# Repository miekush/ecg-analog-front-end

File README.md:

# ECG_Analog_Front_End
Simple Analog Front End for Electrocardiography using INA126 and OPA2337

# License

MKE supports the open source hardware community by sharing hardware design files freely on GitHub!

Please support MKE by purchasing products on [Tindie](https://www.tindie.com/stores/mkengineering/)!

Designed by Mike Kushnerik for MKEngineering

Licensed under [Creative Commons Attribution-ShareAlike CC BY-SA 3.0](http://creativecommons.org/licenses/by-sa/3.0/)

All text above must be included in any redistribution!

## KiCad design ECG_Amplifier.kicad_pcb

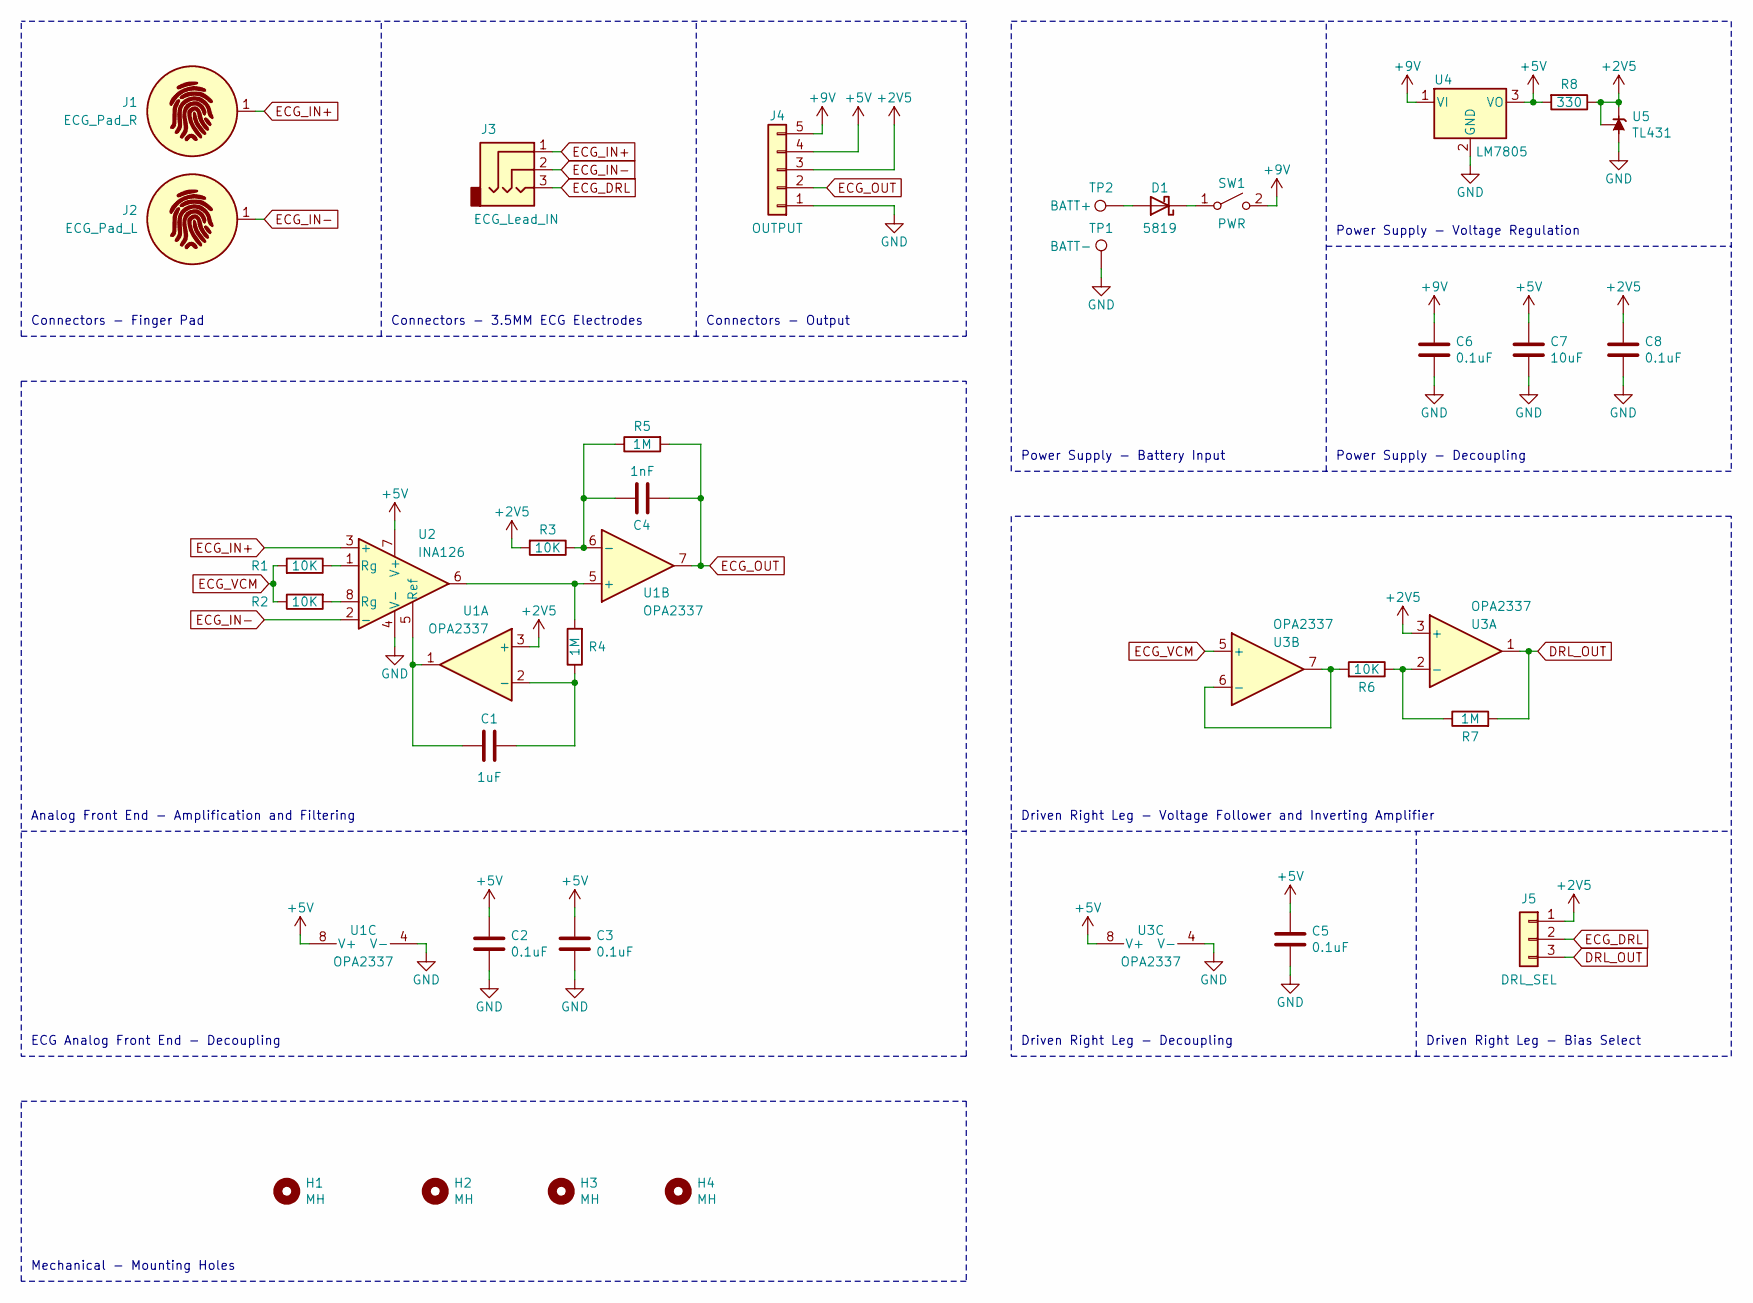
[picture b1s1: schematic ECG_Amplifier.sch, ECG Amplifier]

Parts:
C1: 1uF; C_Disc_D4.3mm_W1.9mm_P5.00mm
C2, C3, C5, C6, C8: 0.1uF; C_Disc_D4.3mm_W1.9mm_P5.00mm
C4: 1nF; C_Disc_D4.3mm_W1.9mm_P5.00mm
C7: 10uF; C_Disc_D4.3mm_W1.9mm_P5.00mm
D1: 5819; D_DO-41_SOD81_P7.62mm_Horizontal
H1, H2, H3, H4: MH; MountingHole_3.2mm_M3
J1: ECG_Pad_R; ECG_Electrode_Pad
J2: ECG_Pad_L; ECG_Electrode_Pad
J3: ECG_Lead_IN; STX-3000
J4: OUTPUT; PinHeader_1x05_P2.54mm_Vertical
J5: DRL_SEL; PinHeader_1x03_P2.54mm_Vertical
R1, R2, R3, R6: 10K; R_Axial_DIN0204_L3.6mm_D1.6mm_P5.08mm_Horizontal
R4, R5, R7: 1M; R_Axial_DIN0204_L3.6mm_D1.6mm_P5.08mm_Horizontal
R8: 330; R_Axial_DIN0204_L3.6mm_D1.6mm_P5.08mm_Horizontal
SW1: PWR; OS102011MS2QN1
TP1: BATT-; WIRE_SR_R
TP2: BATT+; WIRE_SR_C
U1, U3: OPA2337; DIP-8_W7.62mm
U2: INA126; DIP-8_W7.62mm
U4: LM7805; TO-220-3_Horizontal_TabDown
U5: TL431; TO-92_Inline_Wide

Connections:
+2V5: C8.1, J4.3, J5.1, R3.2, R8.1, U1.3 (+), U3.3 (+), U5.1 (REF), U5.3 (K)
+5V: C2.1, C3.1, C5.1, C7.1, J4.4, R8.2, U1.8 (V+), U2.7 (V+), U3.8 (V+), U4.3 (VO)
+9V: C6.1, J4.5, SW1.2 (B), U4.1 (VI)
DRL_OUT: J5.3, R7.2, U3.1
ECG_DRL: J3.3, J5.2
ECG_IN+: J1.1, J3.1, U2.3 (+)
ECG_IN-: J2.1, J3.2, U2.2 (-)
ECG_OUT: C4.2, J4.2, R5.2, U1.7
ECG_VCM: R1.2, R2.1, U3.5 (+)
GND: C2.2, C3.2, C5.2, C6.2, C7.2, C8.2, J4.1, TP1.1, U1.4 (V-), U2.4 (V-), U3.4 (V-), U4.2 (GND), U5.2 (A)
unnamed: C1.1, R4.1, U1.2 (-)
unnamed: C1.2, U1.1, U2.5 (Ref)
unnamed: C4.1, R3.1, R5.1, U1.6 (-)
unnamed: D1.1 (K), SW1.1 (A)
unnamed: D1.2 (A), TP2.1
unnamed: R1.1, U2.1 (Rg)
unnamed: R2.2, U2.8 (Rg)
unnamed: R4.2, U1.5 (+), U2.6
unnamed: R6.1, R7.1, U3.2 (-)
unnamed: R6.2, U3.6 (-), U3.7

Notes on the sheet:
Connectors - Finger Pad
Driven Right Leg - Decoupling
Power Supply - Battery Input
Connectors - 3.5MM ECG Electrodes
Connectors - Output
Power Supply - Voltage Regulation
Power Supply - Decoupling
Mechanical - Mounting Holes
Driven Right Leg - Voltage Follower and Inverting Amplifier
Driven Right Leg - Bias Select
Analog Front End - Amplification and Filtering
ECG Analog Front End - Decoupling

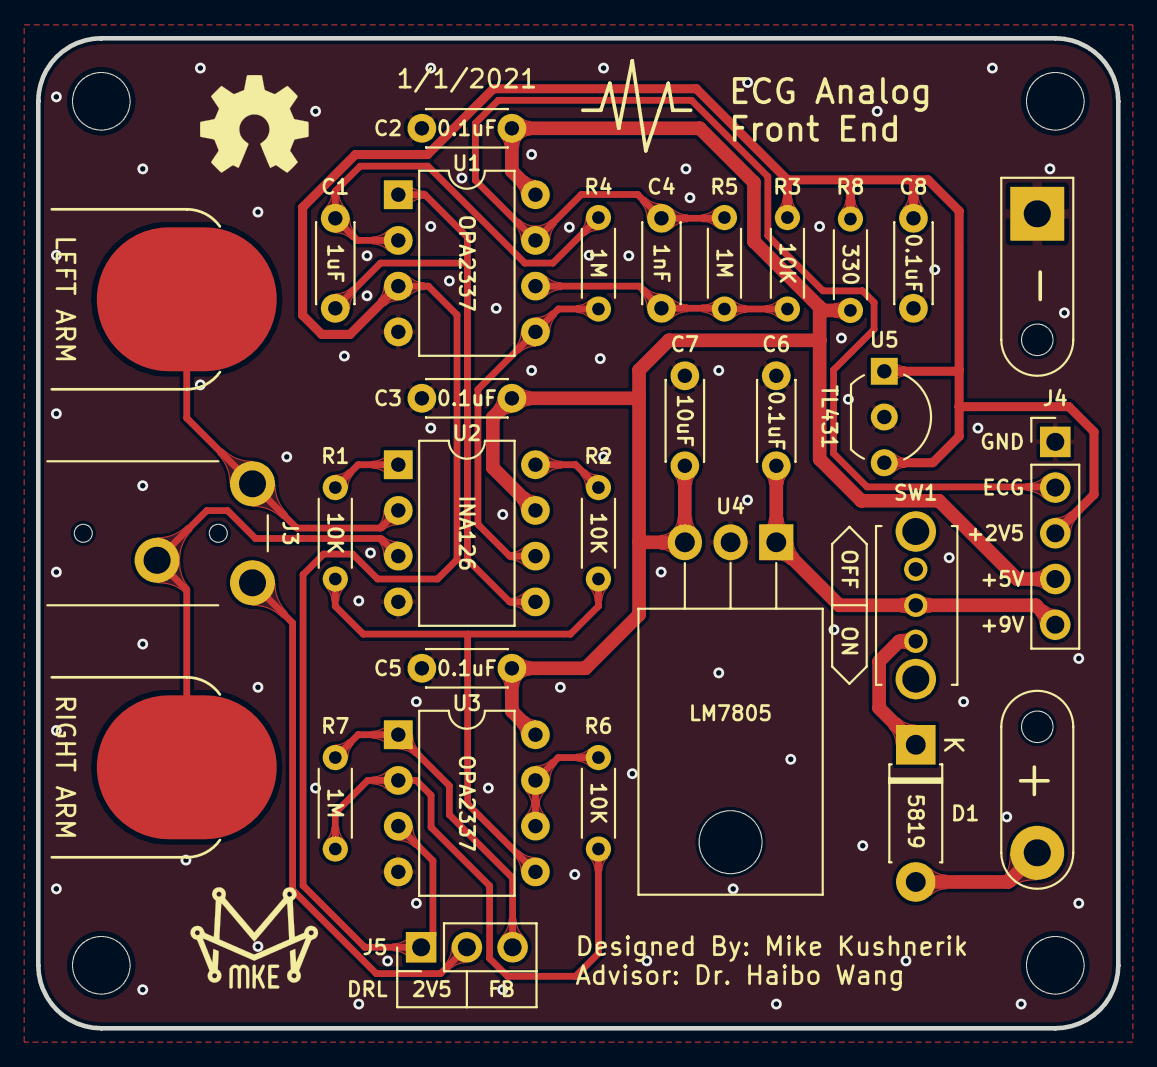
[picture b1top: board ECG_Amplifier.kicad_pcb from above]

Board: 2 copper layers, 60.0 x 55.0 mm, 34 parts (0 on the bottom side), 20 nets.

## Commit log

2021-01-07 Add KiCad Files
2021-01-08 Update License
2021-01-08 Update Images and License
2021-01-08 Add Images

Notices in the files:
ECG_Amplifier.sch:
http://creativecommons.org/licenses/by-sa/4.0
Licensed under Creative Commons Attribution-ShareAlike CC BY-SA 4.0
